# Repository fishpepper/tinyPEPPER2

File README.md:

# tinyPEPPER2 -- a tiny and lightweight 4in1 BLHeli_S ESC -- 2S edition

My approach to build a small and lightweight ESC.

See [http://fishpepper.de/projects/tinyPEPPER2](http://fishpepper.de/projects/tinyPEPPER2) for more details.

As [my previous tinyPEPPER 1S design](http://fishpepper.de/projects/tinyPEPPER), this thing is TINY as well! The outer dimensions are 20x20mm with a 16mm hole-to-hole spacing.
Of course it also runs BLHELI_S.

Key features:
- 16x16mm hole-to-hole spacing
- 1.4g (!)
- BLHeli_S with DSHOT300
- 1S or 2S operation
- 4.8 A continous current

This work is published under the CERN open hardware license v1.2. 
Feel free to use the design - but make sure to give proper credit 
and release all modifications under the same license! 
See LICENSE.txt for details!

THIS COMES WITH NO WARRANTY! BUILD, FLY, AND USE AT YOUR OWN RISK!

# Build your own

Make sure to init the git submodule for the libraries in the
kicad_misc directory by calling git submodule init && git submodule update.
You will have to use a recent kicad version, i used the commit #efdfaeb
when i designed this circuit board. Older versions will probably not work.

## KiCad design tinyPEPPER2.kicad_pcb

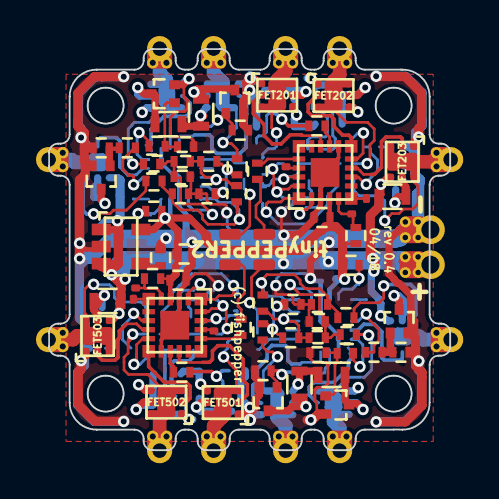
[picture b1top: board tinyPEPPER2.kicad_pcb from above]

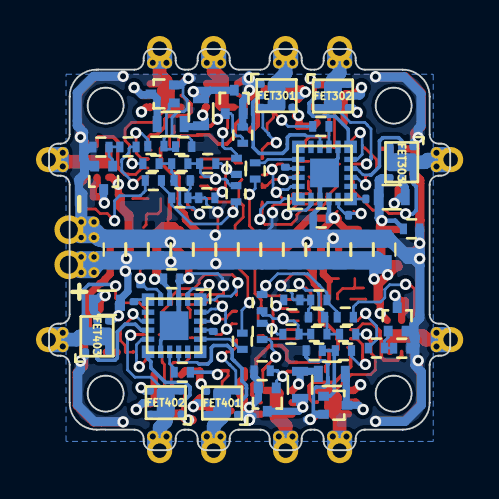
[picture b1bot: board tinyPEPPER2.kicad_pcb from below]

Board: 4 copper layers, 22.3 x 22.3 mm, 163 parts (82 on the bottom side), 100 nets.

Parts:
BL_TX201, BL_TX301, BL_TX401, BL_TX501: TP; TP_smd_0.5x0.4
C201, C301, C401, C501, C1001, C1002: 100n; C_0402_CUSTOM
C202, C203, C204, C302, C303, C304, C402, C403, C404, C502, C503, C504, C1000: 22u; C_0603_CUSTOM
C1003: 10n; C_0402_CUSTOM
FET201, FET202, FET203, FET301, FET302, FET303, FET401, FET402, FET403, FET501, FET502, FET503: UT6MA3; DFN2020-8D
H1, H2, H3, H4: hole; mouting_hole
OUT_A201, OUT_A301, OUT_A401, OUT_A501: TP; TP_PHASE_PAD
OUT_B201, OUT_B301, OUT_B401, OUT_B501: TP; TP_PHASE_PAD
OUT_C201, OUT_C301, OUT_C401, OUT_C501: TP; TP_PHASE_PAD
R201, R220, R301, R320, R401, R420, R501, R520: 1k; R_0402_CUSTOM
R202, R203, R204, R205, R206, R207, R217, R218, R219, R302, R303, R304, R305, R306, R307, R317, R318, R319, R402, R403, R404, R405, R406, R407, R417, R418, R419, R502, R503, R504, R505, R506, R507, R517, R518, R519: 10k; R_0402_CUSTOM
R208, R209, R210, R308, R309, R310, R408, R409, R410, R508, R509, R510: 2k2; R_0402_CUSTOM
R211, R212, R213, R311, R312, R313, R411, R412, R413, R511, R512, R513: 1K; R_0402_CUSTOM
R214, R215, R216, R314, R315, R316, R414, R415, R416, R514, R515, R516: 100; R_0603_CUSTOM
T201, T202, T203, T301, T302, T303, T401, T402, T403, T501, T502, T503: BC847; SC75
TP10, TP12: TP; TP_POWER_PAD_DOUBLESIDED
TP103, TP104, TP105, TP106: TP; tp_SMD_0.6x1.2
TP202, TP203, TP302, TP303, TP402, TP403, TP502, TP503: TP; TP_smd_0.5x0.4
U1: AP131-30; SOT-23-5
U201, U301, U401, U501: EFM8BB10; QFN20

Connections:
/RC_IN_0: R220.1, TP103.1
/RC_IN_1: R320.1, TP104.1
/single esc 1/3V3: C201.2, C301.2, C401.2, C501.2, C1001.1, R201.1, R301.1, R401.1, R501.1, U1.5, U201.4, U301.4, U401.4, U501.4
/single esc 1/Ac_0: R211.2, U201.13
/single esc 1/Ap_0: FET201.2, U201.14
/single esc 1/Bc_0: R212.2, U201.10
/single esc 1/Bp_0: FET202.2, U201.11
/single esc 1/C2CK_0: R201.2, TP203.1, U201.5
/single esc 1/C2D_0: TP202.1, U201.6
/single esc 1/PHASE_A_0: FET201.3, FET201.6, FET201.7, FET201.8, OUT_A201.1, R203.2
/single esc 1/PHASE_B_0: FET202.3, FET202.6, FET202.7, FET202.8, OUT_B201.1, R205.2
/single esc 1/PHASE_C_0: FET203.3, FET203.6, FET203.7, FET203.8, OUT_C201.1, R207.2
/single esc 2/Ac_0: R311.2, U301.13
/single esc 2/Ap_0: FET301.2, U301.14
/single esc 2/Bc_0: R312.2, U301.10
/single esc 2/Bp_0: FET302.2, U301.11
/single esc 2/C2CK_0: R301.2, TP303.1, U301.5
/single esc 2/C2D_0: TP302.1, U301.6
/single esc 2/PHASE_A_0: FET301.3, FET301.6, FET301.7, FET301.8, OUT_A301.1, R303.2
/single esc 2/PHASE_B_0: FET302.3, FET302.6, FET302.7, FET302.8, OUT_B301.1, R305.2
/single esc 2/PHASE_C_0: FET303.3, FET303.6, FET303.7, FET303.8, OUT_C301.1, R307.2
/single esc 3/Ac_0: R411.2, U401.13
/single esc 3/Ap_0: FET401.2, U401.14
/single esc 3/Bc_0: R412.2, U401.10
/single esc 3/Bp_0: FET402.2, U401.11
/single esc 3/C2CK_0: R401.2, TP403.1, U401.5
/single esc 3/C2D_0: TP402.1, U401.6
/single esc 3/PHASE_A_0: FET401.3, FET401.6, FET401.7, FET401.8, OUT_A401.1, R403.2
/single esc 3/PHASE_B_0: FET402.3, FET402.6, FET402.7, FET402.8, OUT_B401.1, R405.2
/single esc 3/PHASE_C_0: FET403.3, FET403.6, FET403.7, FET403.8, OUT_C401.1, R407.2
/single esc 3/RC_IN: R420.1, TP105.1
/single esc 4/Ac_0: R511.2, U501.13
/single esc 4/Ap_0: FET501.2, U501.14
/single esc 4/Bc_0: R512.2, U501.10
/single esc 4/Bp_0: FET502.2, U501.11
/single esc 4/C2CK_0: R501.2, TP503.1, U501.5
/single esc 4/C2D_0: TP502.1, U501.6
/single esc 4/PHASE_A_0: FET501.3, FET501.6, FET501.7, FET501.8, OUT_A501.1, R503.2
/single esc 4/PHASE_B_0: FET502.3, FET502.6, FET502.7, FET502.8, OUT_B501.1, R505.2
/single esc 4/PHASE_C_0: FET503.3, FET503.6, FET503.7, FET503.8, OUT_C501.1, R507.2
/single esc 4/RC_IN: R520.1, TP106.1
GND: C201.1, C202.1, C203.1, C204.1, C301.1, C302.1, C303.1, C304.1, C401.1, C402.1, C403.1, C404.1, C501.1, C502.1, C503.1, C504.1, C1000.1, C1001.2, C1002.2, C1003.2, FET201.1, FET202.1, FET203.1, FET301.1, FET302.1, FET303.1, FET401.1, FET402.1, FET403.1, FET501.1, FET502.1, FET503.1, R208.1, R209.1, R210.1, R217.1, R218.1, R219.1, R308.1, R309.1, R310.1, R317.1, R318.1, R319.1, R408.1, R409.1, R410.1, R417.1, R418.1, R419.1, R508.1, R509.1, R510.1, R517.1, R518.1, R519.1, T201.2, T202.2, T203.2, T301.2, T302.2, T303.2, T401.2, T402.2, T403.2, T501.2, T502.2, T503.2, TP12.1, U1.2, U201.3, U201.12, U201.21, U301.3, U301.12, U301.21, U401.3, U401.12, U401.21, U501.3, U501.12, U501.21
unnamed: BL_TX201.1, U201.18
unnamed: BL_TX301.1, U301.18
unnamed: BL_TX401.1, U401.18
unnamed: BL_TX501.1, U501.18
unnamed: C1003.1, U1.4
unnamed: FET201.5, R214.2, T201.3
unnamed: FET202.5, R215.2, T202.3
unnamed: FET203.2, U201.9
unnamed: FET203.5, R216.2, T203.3
unnamed: FET301.5, R314.2, T301.3
unnamed: FET302.5, R315.2, T302.3
unnamed: FET303.2, U301.9
unnamed: FET303.5, R316.2, T303.3
unnamed: FET401.5, R414.2, T401.3
unnamed: FET402.5, R415.2, T402.3
unnamed: FET403.2, U401.9
unnamed: FET403.5, R416.2, T403.3
unnamed: FET501.5, R514.2, T501.3
unnamed: FET502.5, R515.2, T502.3
unnamed: FET503.2, U501.9
unnamed: FET503.5, R516.2, T503.3
unnamed: R202.1, R204.1, R206.1, U201.19
unnamed: R202.2, R203.1, R208.2, U201.20
unnamed: R204.2, R205.1, R209.2, U201.2
unnamed: R206.2, R207.1, R210.2, U201.1
unnamed: R211.1, R217.2, T201.1
unnamed: R212.1, R218.2, T202.1
unnamed: R213.1, R219.2, T203.1
unnamed: R213.2, U201.8
unnamed: R220.2, U201.17
unnamed: R302.1, R304.1, R306.1, U301.19
unnamed: R302.2, R303.1, R308.2, U301.20
unnamed: R304.2, R305.1, R309.2, U301.2
unnamed: R306.2, R307.1, R310.2, U301.1
unnamed: R311.1, R317.2, T301.1
unnamed: R312.1, R318.2, T302.1
unnamed: R313.1, R319.2, T303.1
unnamed: R313.2, U301.8
unnamed: R320.2, U301.17
unnamed: R402.1, R404.1, R406.1, U401.19
unnamed: R402.2, R403.1, R408.2, U401.20
unnamed: R404.2, R405.1, R409.2, U401.2
unnamed: R406.2, R407.1, R410.2, U401.1
unnamed: R411.1, R417.2, T401.1
unnamed: R412.1, R418.2, T402.1
unnamed: R413.1, R419.2, T403.1
unnamed: R413.2, U401.8
unnamed: R420.2, U401.17
unnamed: R502.1, R504.1, R506.1, U501.19
unnamed: R502.2, R503.1, R508.2, U501.20
unnamed: R504.2, R505.1, R509.2, U501.2
unnamed: R506.2, R507.1, R510.2, U501.1
unnamed: R511.1, R517.2, T501.1
unnamed: R512.1, R518.2, T502.1
unnamed: R513.1, R519.2, T503.1
unnamed: R513.2, U501.8
unnamed: R520.2, U501.17
VCC: C202.2, C203.2, C204.2, C302.2, C303.2, C304.2, C402.2, C403.2, C404.2, C502.2, C503.2, C504.2, C1000.2, C1002.1, FET201.4, FET202.4, FET203.4, FET301.4, FET302.4, FET303.4, FET401.4, FET402.4, FET403.4, FET501.4, FET502.4, FET503.4, R214.1, R215.1, R216.1, R314.1, R315.1, R316.1, R414.1, R415.1, R416.1, R514.1, R515.1, R516.1, TP10.1, U1.1, U1.3

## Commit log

2017-02-22 init
2017-02-22 update lib to master
2017-02-22 adding gate druiver
2017-02-23 routing test done
2017-02-23 4in1
2017-02-23 caps
2017-02-23 first routing ok
2017-02-23 cosmetics
2017-02-24 added serial R
2017-02-24 4layer done
2017-02-24 minor cleanup of traces
2017-03-06 added docs
2017-03-09 fixed npn T
2017-03-09 upd doc
2017-03-15 new pads
2018-04-13 fixing sch
